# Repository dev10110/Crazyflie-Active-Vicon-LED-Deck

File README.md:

# Crazyflie-Active-Vicon-LED-Deck

This repo contains the PCB layout for a vicon active marker deck for crazyflies. 

The PCB was designed in Kicad9, following the reference schematics of the [BitCraze LED Deck](https://www.bitcraze.io/products/led-ring-deck/), and the [ETH-PBL Active Vicon Marker Deck](https://github.com/ETH-PBL/Active-motion-capture-marker-deck).

The main components on the board are 
- 850 nm LED [HIR19-21C/L11/TR8](https://www.digikey.com/en/products/detail/everlight-electronics-co-ltd/HIR19-21C-L11-TR8/2675838)
- 4x RGB LED [WS2812B](https://jlcpcb.com/api/file/downloadByFileSystemAccessId/8588893982302875648)
- Buck-Boost Converter (to mainain 3.8V) [STBB1-APUR](https://www.st.com/resource/en/datasheet/stbb1-axx.pdf)
- One-Wire Memory EEPROM [DS28E05R+T](https://www.analog.com/media/en/technical-documentation/data-sheets/DS28E05.pdf)

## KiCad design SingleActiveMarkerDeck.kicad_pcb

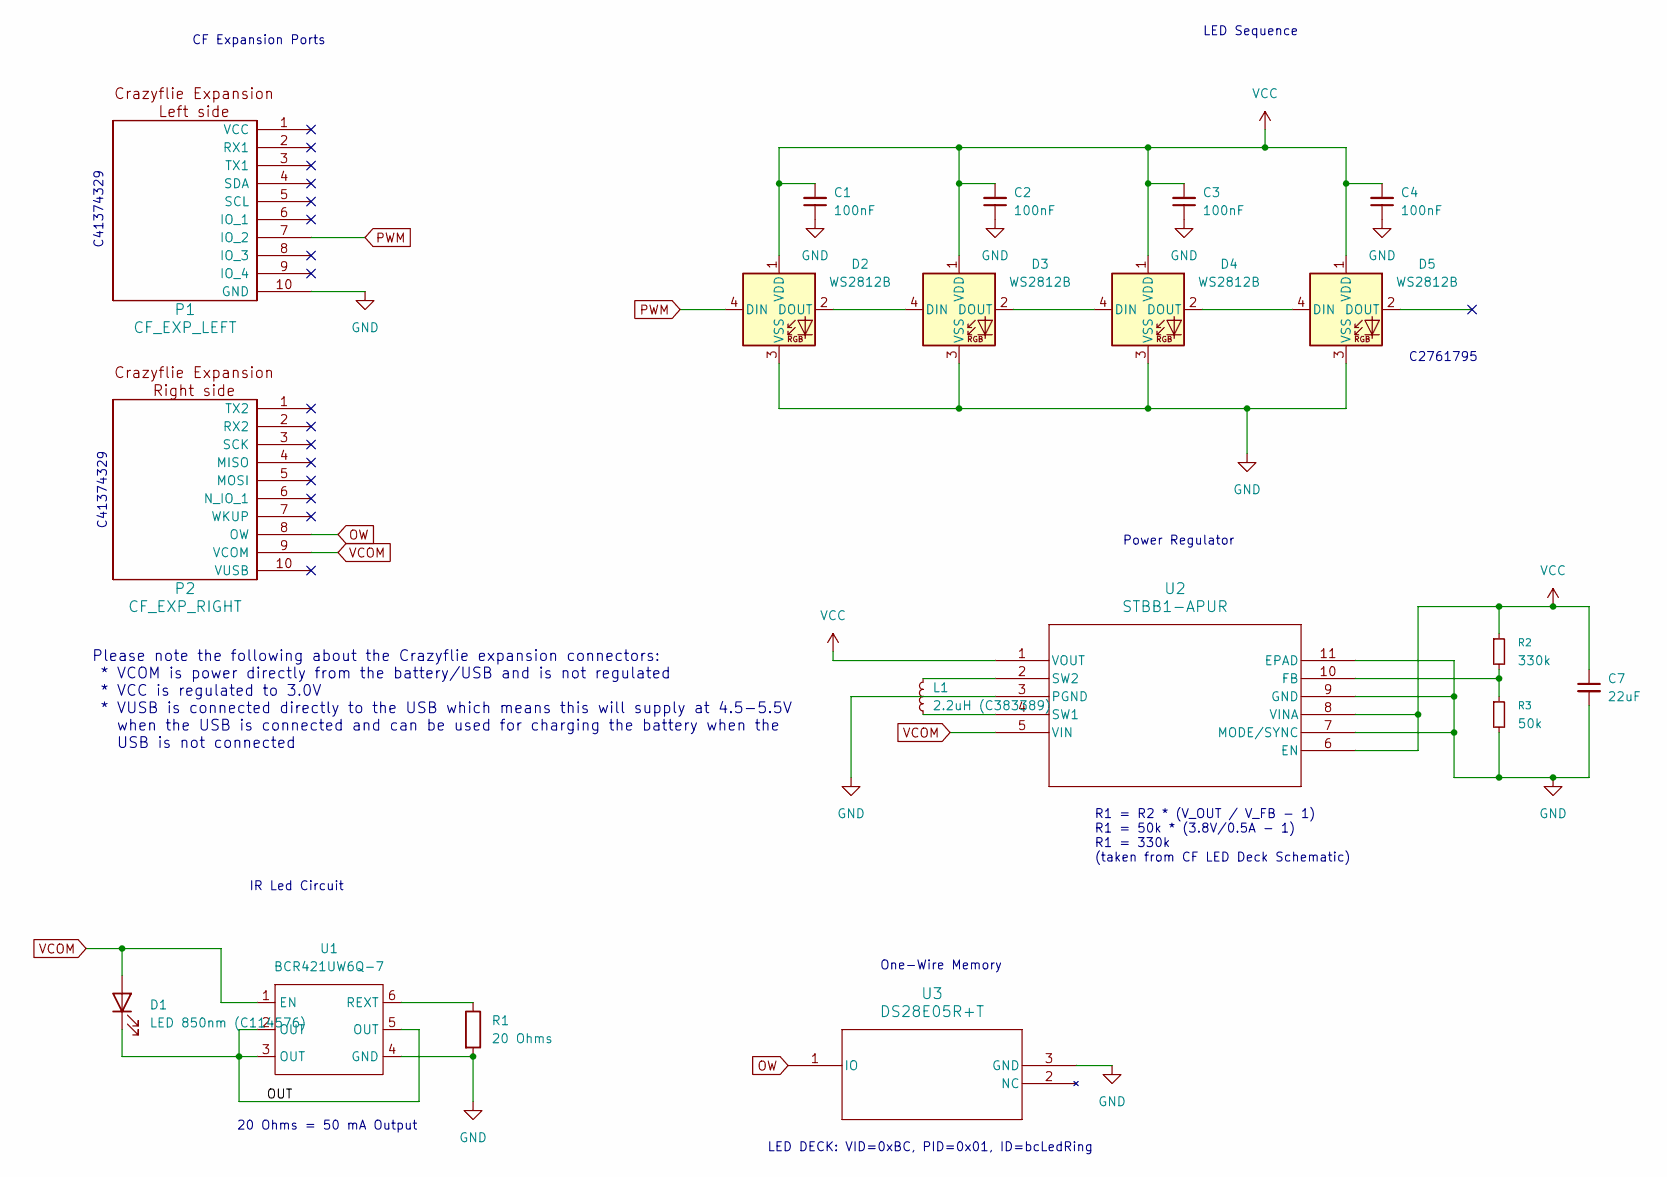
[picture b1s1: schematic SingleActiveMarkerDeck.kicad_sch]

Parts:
C1, C2, C3, C4: 100nF; C_0402_1005Metric
C7: 22uF; C_0603_1608Metric
D1: LED 850nm (C114576); LED_0603_1608Metric
D2, D3, D4, D5: WS2812B; LED_WS2812B_PLCC4_5.0x5.0mm_P3.2mm
L1: 2.2uH (C383389); L_0402_1005Metric
P1: CF_EXP_LEFT
P2: CF_EXP_RIGHT
R1: 20 Ohms; R_0603_1608Metric
R2: 330k; R_0603_1608Metric
R3: 50k; R_0603_1608Metric
U1: BCR421UW6Q-7; SOT-23-6
U2: STBB1-APUR; SON_B1-APUR_STM
U3: DS28E05R+T; 21-0051H_MXM

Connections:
/OUT: D1.1 (K), U1.2 (OUT), U1.3 (OUT), U1.5 (OUT)
GND: C1.1, C2.1, C3.1, C4.1, C7.2, D2.3 (VSS), D3.3 (VSS), D4.3 (VSS), D5.3 (VSS), P1.10 (GND), R1.2, R3.2, U1.4 (GND), U2.3 (PGND), U2.7 (MODE/SYNC), U2.9 (GND), U2.11 (EPAD), U3.3 (GND)
unnamed: D2.2 (DOUT), D3.4 (DIN)
unnamed: D3.2 (DOUT), D4.4 (DIN)
unnamed: D4.2 (DOUT), D5.4 (DIN)
unnamed: R1.1, U1.6 (REXT)
unnamed: R2.2, R3.1, U2.10 (FB)
unnamed: L1.1, U2.4 (SW1)
unnamed: L1.2, U2.2 (SW2)
OW: P2.8 (OW), U3.1 (IO)
PWM: D2.4 (DIN), P1.7 (IO_2)
VCC: C1.2, C2.2, C3.2, C4.2, C7.1, D2.1 (VDD), D3.1 (VDD), D4.1 (VDD), D5.1 (VDD), R2.1, U2.1 (VOUT), U2.6 (EN), U2.8 (VINA)
VCOM: D1.2 (A), P2.9 (VCOM), U1.1 (EN), U2.5 (VIN)

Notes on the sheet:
C2761795
LED Sequence
CF Expansion Ports
R1 = R2 * (V_OUT / V_FB - 1) R1 = 50k * (3.8V/0.5A - 1) R1 = 330k (taken from CF LED Deck Schematic)
C41374329
IR Led Circuit
One-Wire Memory
Power Regulator
20 Ohms = 50 mA Output
LED DECK: VID=0xBC, PID=0x01, ID=bcLedRing
Please note the following about the Crazyflie expansion connectors: * VCOM is power directly from the battery/USB and is not regulated * VCC is regulated to 3.0V * VUSB is connected directly to the USB which means this will supply at 4.5-5.5V when the USB is connected and can be used for charging t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

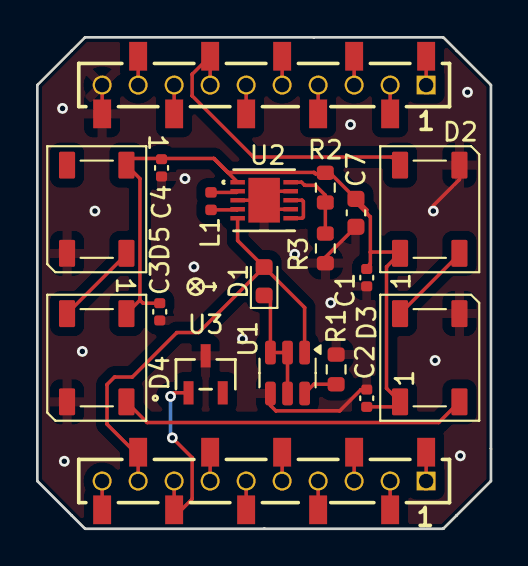
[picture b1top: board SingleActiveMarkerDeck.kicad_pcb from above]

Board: 2 copper layers, 25.2 x 27.3 mm, 19 parts (0 on the bottom side), 13 nets.

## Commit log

2025-08-07 typo
2025-08-07 added PDF of schematic
